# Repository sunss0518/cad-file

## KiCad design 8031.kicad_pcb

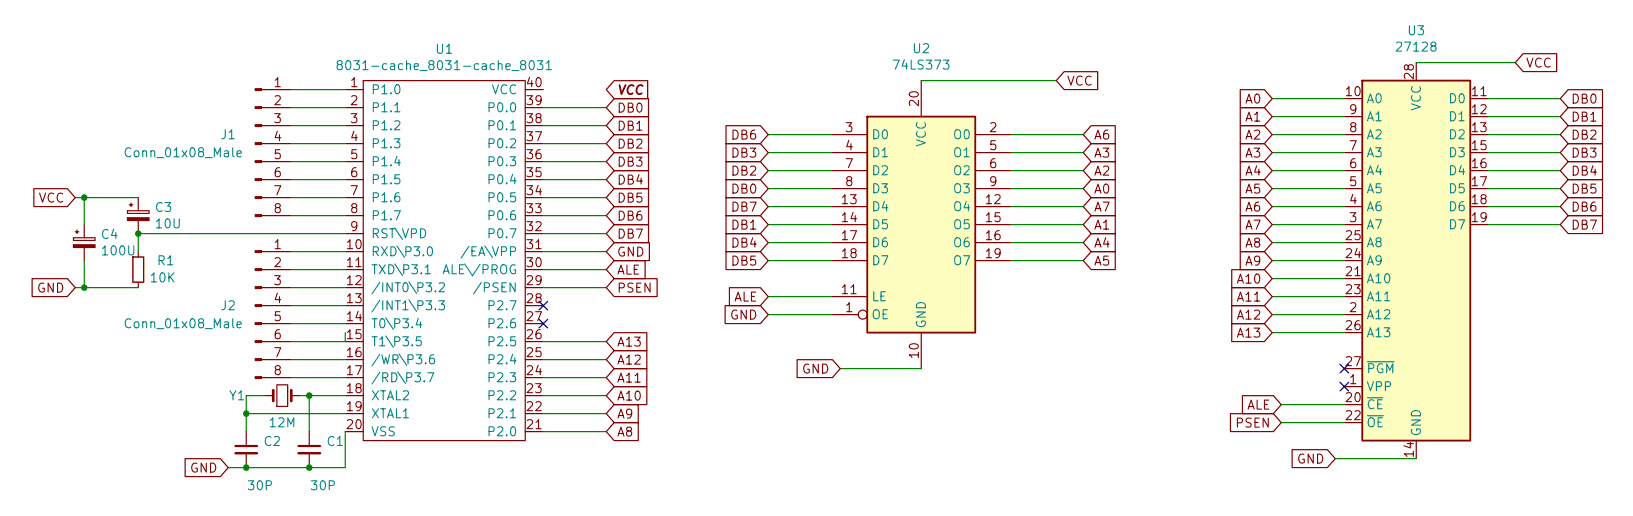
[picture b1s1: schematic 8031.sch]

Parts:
C1, C2: 30P; C_Disc_D3.4mm_W2.1mm_P2.50mm
C3: 10U; CP_Radial_D4.0mm_P1.50mm
C4: 100U; CP_Radial_D6.3mm_P2.50mm
J1, J2: Conn_01x08_Male; PinHeader_1x08_P2.54mm_Vertical
R1: 10K; R_Axial_DIN0204_L3.6mm_D1.6mm_P7.62mm_Horizontal
U1: 8031-cache_8031-cache_8031; DIP-40_W15.24mm
U2: 74LS373; DIP-20_W7.62mm
U3: 27128; DIP-28_W15.24mm
Y1: 12M; Crystal_HC18-U_Vertical

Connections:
A0: U2.9 (O3), U3.10 (A0)
A1: U2.15 (O5), U3.9 (A1)
A2: U2.6 (O2), U3.8 (A2)
A3: U2.5 (O1), U3.7 (A3)
A4: U2.16 (O6), U3.6 (A4)
A5: U2.19 (O7), U3.5 (A5)
A6: U2.2 (O0), U3.4 (A6)
A7: U2.12 (O4), U3.3 (A7)
A8: U1.21 (P2.0), U3.25 (A8)
A9: U1.22 (P2.1), U3.24 (A9)
A10: U1.23 (P2.2), U3.21 (A10)
A11: U1.24 (P2.3), U3.23 (A11)
A12: U1.25 (P2.4), U3.2 (A12)
A13: U1.26 (P2.5), U3.26 (A13)
ALE: U1.30 (ALE\/PROG), U2.11 (LE), U3.20 (~CE)
DB0: U1.39 (P0.0), U2.8 (D3), U3.11 (D0)
DB1: U1.38 (P0.1), U2.14 (D5), U3.12 (D1)
DB2: U1.37 (P0.2), U2.7 (D2), U3.13 (D2)
DB3: U1.36 (P0.3), U2.4 (D1), U3.15 (D3)
DB4: U1.35 (P0.4), U2.17 (D6), U3.16 (D4)
DB5: U1.34 (P0.5), U2.18 (D7), U3.17 (D5)
DB6: U1.33 (P0.6), U2.3 (D0), U3.18 (D6)
DB7: U1.32 (P0.7), U2.13 (D4), U3.19 (D7)
GND: C1.2, C2.2, C4.2, R1.2, U1.20 (VSS), U1.31 (/EA\VPP), U2.1 (OE), U2.10 (GND), U3.14 (GND)
unnamed: C1.1, U1.18 (XTAL2), Y1.2
unnamed: C2.1, U1.19 (XTAL1), Y1.1
unnamed: C3.2, R1.1, U1.9 (RST\VPD)
unnamed: J1.1, U1.1 (P1.0)
unnamed: J1.2, U1.2 (P1.1)
unnamed: J1.3, U1.3 (P1.2)
unnamed: J1.4, U1.4 (P1.3)
unnamed: J1.5, U1.5 (P1.4)
unnamed: J1.6, U1.6 (P1.5)
unnamed: J1.7, U1.7 (P1.6)
unnamed: J1.8, U1.8 (P1.7)
unnamed: J2.1, U1.10 (RXD\P3.0)
unnamed: J2.2, U1.11 (TXD\P3.1)
unnamed: J2.3, U1.12 (/INT0\P3.2)
unnamed: J2.4, U1.13 (/INT1\P3.3)
unnamed: J2.5, U1.14 (T0\P3.4)
unnamed: J2.6, U1.15 (T1\P3.5)
unnamed: J2.7, U1.16 (/WR\P3.6)
unnamed: J2.8, U1.17 (/RD\P3.7)
PSEN: U1.29 (/PSEN), U3.22 (~OE)
VCC: C3.1, C4.1, U1.40 (VCC), U2.20 (VCC), U3.28 (VCC)

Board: 2 copper layers, 11 parts (0 on the bottom side), 45 nets, no tracks yet.

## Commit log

2022-07-29 8031b
